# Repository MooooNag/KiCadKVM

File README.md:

# KiCadKVM

In this repository a functional USB 2.0 K(V)M is created in KiCad

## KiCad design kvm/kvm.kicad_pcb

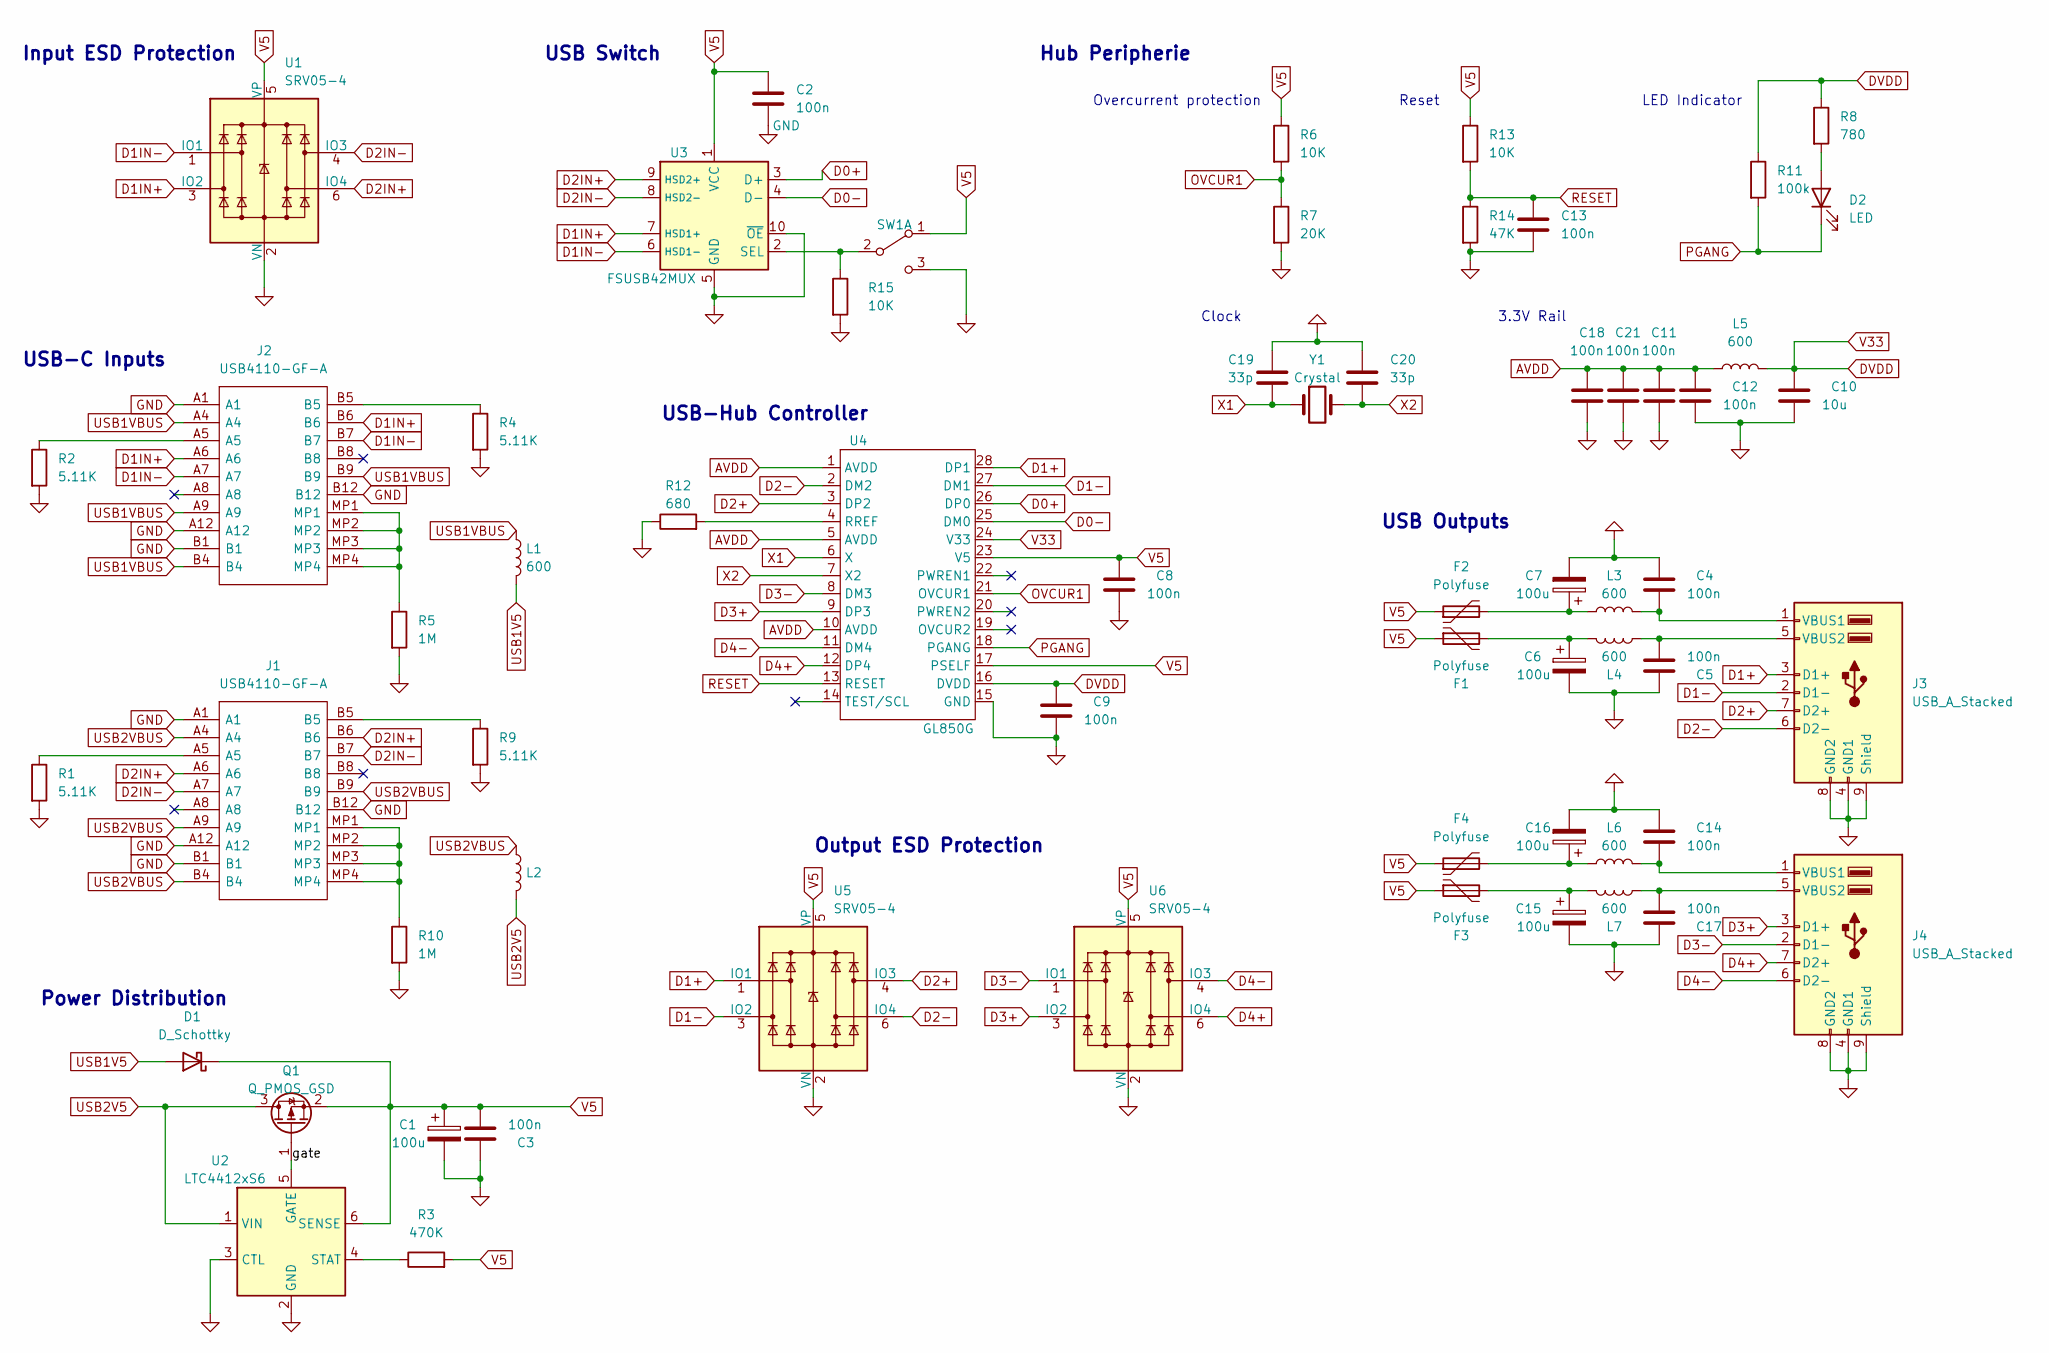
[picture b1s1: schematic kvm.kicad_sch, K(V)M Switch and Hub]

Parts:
C1, C6, C7, C15, C16: 100u; CP_Radial_D5.0mm_P2.00mm
C2, C3, C4, C5, C8, C9, C11, C12, C13, C14, C17, C18, C21: 100n; C_0603_1608Metric_Pad1.08x0.95mm_HandSolder
C10: 10u; C_0805_2012Metric_Pad1.18x1.45mm_HandSolder
C19, C20: 33p; C_0603_1608Metric_Pad1.08x0.95mm_HandSolder
D1: D_Schottky; D_SOD-123F
D2: LED; LED_0805_2012Metric_Pad1.15x1.40mm_HandSolder
F1, F2, F3, F4: Polyfuse; Fuse_1206_3216Metric_Pad1.42x1.75mm_HandSolder
J1, J2: USB4110-GF-A; USB4110GFA; Mouser Part Number 640-USB4110-GF-A
J3, J4: USB_A_Stacked; USB_A_Wuerth_61400826021_Horizontal_Stacked
L1, L2, L3, L4, L5, L6, L7: 600; R_0603_1608Metric_Pad0.98x0.95mm_HandSolder
Q1: Q_PMOS_GSD; SOT-23-3
R1, R2, R4, R9: 5.11K; R_0603_1608Metric_Pad0.98x0.95mm_HandSolder
R3: 470K; R_0603_1608Metric_Pad0.98x0.95mm_HandSolder
R5, R10: 1M; R_0603_1608Metric_Pad0.98x0.95mm_HandSolder
R6, R13, R15: 10K; R_0603_1608Metric_Pad0.98x0.95mm_HandSolder
R7: 20K; R_0603_1608Metric_Pad0.98x0.95mm_HandSolder
R8: 780; R_0603_1608Metric_Pad0.98x0.95mm_HandSolder
R11: 100k; R_0603_1608Metric_Pad0.98x0.95mm_HandSolder
R12: 680; R_0603_1608Metric_Pad0.98x0.95mm_HandSolder
R14: 47K; R_0603_1608Metric_Pad0.98x0.95mm_HandSolder
SW1: SW_DPDT_x2; PinHeader_1x03_P2.54mm_Vertical
U1, U5, U6: SRV05-4; SOT-23-6
U2: LTC4412xS6; TSOT-23-6
U3: FSUSB42MUX; MSOP-10_3x3mm_P0.5mm
U4: GL850G; SSOP-28_5.3x10.2mm_P0.65mm
Y1: Crystal; ECS120184XCKM

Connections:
/gate: Q1.1 (G), U2.5 (GATE)
AVDD: C11.1, C12.1, C18.1, C21.1, L5.1, U4.1 (AVDD), U4.5 (AVDD), U4.10 (AVDD)
D0+: U3.3 (D+), U4.26 (DP0)
D0-: U3.4 (D-), U4.25 (DM0)
D1+: J3.3 (D1+), U4.28 (DP1), U5.1 (IO1)
D1-: J3.2 (D1-), U4.27 (DM1), U5.3 (IO2)
D1IN+: J2.A6, J2.B6, U1.3 (IO2), U3.7 (HSD1+)
D1IN-: J2.A7, J2.B7, U1.1 (IO1), U3.6 (HSD1-)
D2+: J3.7 (D2+), U4.3 (DP2), U5.4 (IO3)
D2-: J3.6 (D2-), U4.2 (DM2), U5.6 (IO4)
D2IN+: J1.A6, J1.B6, U1.6 (IO4), U3.9 (HSD2+)
D2IN-: J1.A7, J1.B7, U1.4 (IO3), U3.8 (HSD2-)
D3+: J4.3 (D1+), U4.9 (DP3), U6.3 (IO2)
D3-: J4.2 (D1-), U4.8 (DM3), U6.1 (IO1)
D4+: J4.7 (D2+), U4.12 (DP4), U6.6 (IO4)
D4-: J4.6 (D2-), U4.11 (DM4), U6.4 (IO3)
DVDD: C9.1, C10.1, L5.2, R8.1, R11.1, U4.16 (DVDD), U4.24 (V33)
GND: C1.2, C2.2, C3.1, C4.1, C5.1, C6.2, C7.2, C8.2, C9.2, C10.2, C11.2, C12.2, C13.2, C14.1, C15.2, C16.2, C17.1, C18.2, C19.1, C20.1, C21.2, J1.A1, J1.A12, J1.B1, J1.B12, J2.A1, J2.A12, J2.B1, J2.B12, J3.4 (GND1), J3.8 (GND2), J3.9 (Shield), J4.4 (GND1), J4.8 (GND2), J4.9 (Shield), R1.2, R2.2, R4.2, R5.2, R7.2, R9.2, R10.2, R12.1, R14.2, R15.2, SW1.3 (C), U1.2 (VN), U2.2 (GND), U2.3 (CTL), U3.5 (GND), U3.10 (~OE), U4.15 (GND), U5.2 (VN), U6.2 (VN)
unnamed: C4.2, J3.1 (VBUS1), L3.2
unnamed: C5.2, J3.5 (VBUS2), L4.2
unnamed: C6.1, F1.2, L4.1
unnamed: C7.1, F2.2, L3.1
unnamed: C14.2, J4.1 (VBUS1), L6.2
unnamed: C15.1, F3.2, L7.1
unnamed: C16.1, F4.2, L6.1
unnamed: C17.2, J4.5 (VBUS2), L7.2
unnamed: D2.2 (A), R8.2
unnamed: J1.A5, R1.1
unnamed: J1.B5, R9.1
unnamed: J1.MP1, J1.MP2, J1.MP3, J1.MP4, R10.1
unnamed: J2.A5, R2.1
unnamed: J2.B5, R4.1
unnamed: J2.MP1, J2.MP2, J2.MP3, J2.MP4, R5.1
unnamed: R3.1, U2.4 (STAT)
unnamed: R12.2, U4.4 (RREF)
unnamed: R15.1, SW1.2 (B), U3.2 (SEL)
OVCUR1: R6.2, R7.1, U4.21 (OVCUR1)
PGANG: D2.1 (K), R11.2, U4.18 (PGANG)
RESET: C13.1, R13.2, R14.1, U4.13 (RESET)
USB1V5: D1.2 (A), L1.2
USB1VBUS: J2.A4, J2.A9, J2.B4, J2.B9, L1.1
USB2V5: L2.2, Q1.3 (D), U2.1 (VIN)
USB2VBUS: J1.A4, J1.A9, J1.B4, J1.B9, L2.1
V5: C1.1, C2.1, C3.2, C8.1, D1.1 (K), F1.1, F2.1, F3.1, F4.1, Q1.2 (S), R3.2, R6.1, R13.1, SW1.1 (A), U1.5 (VP), U2.6 (SENSE), U3.1 (VCC), U4.17 (PSELF), U4.23 (V5), U5.5 (VP), U6.5 (VP)
X1: C19.2, U4.6 (X), Y1.1
X2: C20.2, U4.7 (X2), Y1.2

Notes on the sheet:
USB Outputs
Clock
LED Indicator
Hub Peripherie
Power Distribution
USB-Hub Controller
Output ESD Protection
Input ESD Protection
3.3V Rail
Overcurrent protection
USB-C Inputs
Reset
USB Switch

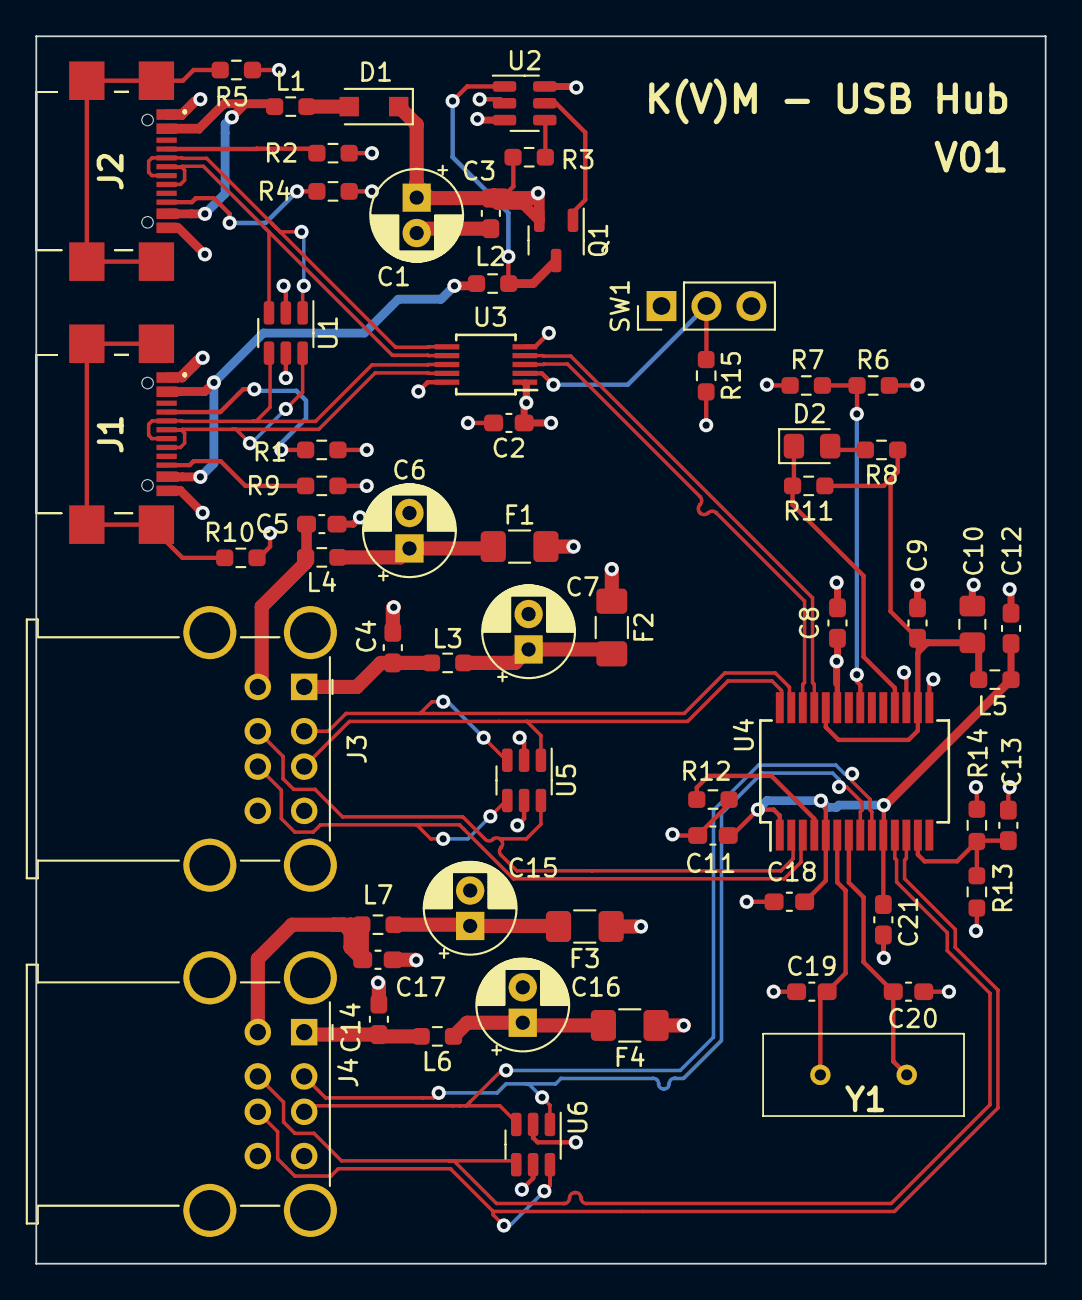
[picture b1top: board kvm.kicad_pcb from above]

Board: 4 copper layers, 57.0 x 69.3 mm, 62 parts (0 on the bottom side), 46 nets.

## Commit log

2022-12-25 added inital project files^:x
2023-01-08 updated git ignore
2023-01-08 added schematic
2023-01-08 SCH: output side finished
2023-01-08 schematic done, footprints missing
2023-01-09 finished schematic
2023-01-09 first layout version
2023-01-11 first pcb layout
2023-01-11 small layout changes
2023-01-12 replaced USB-C ports with smd parts
2023-01-12 updated layout
2023-01-12 reanotated on pcb
2023-01-13 recheck drc
2023-01-14 fixed drc
2023-01-17 added gerber files
2023-01-17 added fabrication zip file
2023-01-17 added buy links
2023-01-17 added mouser links to all components
2023-02-16 updated link to 100nF caps
2023-02-19 added 3D models
2023-02-19 added image to readme
2023-02-19 moved image folder
2023-03-02 fixed missing pull down on FSUSBMUX
2023-03-02 removed unused file
